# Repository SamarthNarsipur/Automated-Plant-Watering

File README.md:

Automated Plant Care v1 

yo, welcome to version 1! i built a custom arduino nano backpack shield because i wanted something sleek and tiny that won't look like a giant brick sitting next to my small plants.

what this hardware actually does

basically, i always forget to water my plants. so this board has a soil moisture sensor probe that sits in the dirt and acts like its eyes. if the dirt gets super dry, the arduino detects it and flashes a signal over to a pn2222a transistor switch. the transistor acts like an inline electronic gate keeper, allowing current to flood down into a mini 5v submersible water pump to give the plant a quick 4-second drink. then it sleeps for a minute and loops forever.
it is completely autonomous so my plants can survive my terrible memory.
i also left some digital and analog pins wide open on the nano footprint header layout. that way, if i want to upgrade it later down the line, i can easily breakout wires for an oled screen display to track live moisture metrics or plug in a second pump channel for another plant pot without rebuilding the entire power switching grid from scratch.

how to set it up

to build this thing yourself, you just need to get the custom fiberglass pcb manufactured using the production files included in this repository. once the board arrives in your mail, grab a basic soldering iron kit and solder the male pin headers for the nano, the small 1k ohm resistor, and the npn switching transistor right into their labeled places.
after the soldering is finished, just pop your arduino nano into the sockets, hook up your external 5v pump wires and moisture probe line to the terminal plugs, and use the arduino ide software on your laptop to upload the main code script down a standard usb cable.

files in this repo

• Gerbers_v2.zip - the actual production blueprints for the factory machines to print out the copper lines and fiberglass layers.
• main.ino - the tiny script that tells the microcontroller when to flip the switch.
• BOM.md - the shopping list and links for parts (plus a soldering iron kit because i dont have any solder wire at home yet lol).
built for hack club forge! 

onshape links for the case
1. https://cad.onshape.com/documents/dc3bb86a8ae5408e919ddfb3/w/a6c21399b65a292ff43e633e/e/870f76d3df2bffd9df0bdc23
2. https://cad.onshape.com/documents/dc3bb86a8ae5408e919ddfb3/w/a6c21399b65a292ff43e633e/e/acd912c24c61a0c706c50cb3
# Bill of Materials (BOM) & Budget - Automated Plant Care v1

| Designator | Component Name | Description / Package | Qty | Cost (INR) | Cost (USD Approx.) | Direct Purchase Link |
| :--- | :--- | :--- | :--- | :--- | :--- | :--- |
| **A1** | Arduino Nano R3 | ATmega328P MCU (Unsoldered headers) | 1 | ₹229.00 | $2.75 | [Robu Arduino Nano Page](https://robu.in/product/arduino-nano-board-r3-ch340-chip-with-usb-cable-solderedarduino-nano-r3-usb-cable/) |
| **Q1** | PN2222A / 2N2222 | NPN Bipolar Switching Transistor (TO-92) | 1 | ₹2.25 | $0.03 | [Robu 2N2222 Transistor Page](https://robu.in/product/2n2222a-slkorslkormicro-elec-40v-600ma-npn-to-92-bipolar-bjt-rohs/) |
| **R1** | Through-Hole Resistor | 1k Ohm Metal Film Axial Resistor (1/4W Kit) | 1 | ₹299.00 | $3.60 | [Robu Resistor Kit Page](https://robu.in/product/100pcs-1-4w-metal-film-resistors-assortment-for-diy-electronic-projects-and-experiments-2/) |
| **J3 / J4** | 2.54mm Breakaway Headers | Single Row Straight Male Pin Header Strip | 1 | ₹15.00 | $0.18 | [Robu Pin Header Page](https://robu.in/product/2-54mm-1x40-pin-male-single-row-straight-long-header-strip-pack-of-3/) |
| **External** | Soil Moisture Sensor | Soil Humidity Meter / Probe Module Kit | 1 | ₹125.00 | $1.50 | [Robu Moisture Sensor Page](https://robu.in/product/soil-moisture-module-soil-moisture-detection/) |
| **External** | Mini Water Pump | 3V-5V Micro Submersible DC Motor Water Pump | 1 | ₹145.00 | $1.75 | [Robu Mini Pump Page](https://robu.in/product/wps27-12v-dc-1l-min-mini-water-pump/) |
| **Tools** | Soldering Iron Kit | 25W Soldering Iron Combo Kit with Accessories | 1 | ₹739.00 | $8.90 | [Robu Soldering Kit Page](https://robu.in/product/soldering-iron-kit-3-in-1/) |
| **Prototyping**| Breadboard | Solderless Breadboard (830 Points / Full Size) | 1 | ₹99.00 | $1.20 | [Direct Product Link](https://robu.in/product/mb102-830-points-solderless-prototype-pcb-breadboard-high-quality/) |
| **Wires - MM**| Jumper Wires M-M | Male-to-Male DuPont Ribbon Cable (40-Pin 30cm) | 1 | ₹79.00 | $0.95 | [Direct Product Link](https://robu.in/product/male-to-male-jumper-wires-40-pin-30cm/) |
| **Wires - MF**| Jumper Wires M-F | Male-to-Female DuPont Ribbon Cable (40-Pin 20cm) | 1 | ₹49.00 | $0.60 | [Direct Product Link](https://robu.in/product/male-to-female-jumper-wires-40pcs-20cm/) |
| **Wires - FF**| Jumper Wires F-F | Female-to-Female DuPont Ribbon Cable (40-Pin 20cm)| 1 | ₹49.00 | $0.60 | [Direct Product Link](https://robu.in/product/20cm-dupont-wire-color-jumper-cable-2-54mm-1p-1p-female-female-40pcs/) |

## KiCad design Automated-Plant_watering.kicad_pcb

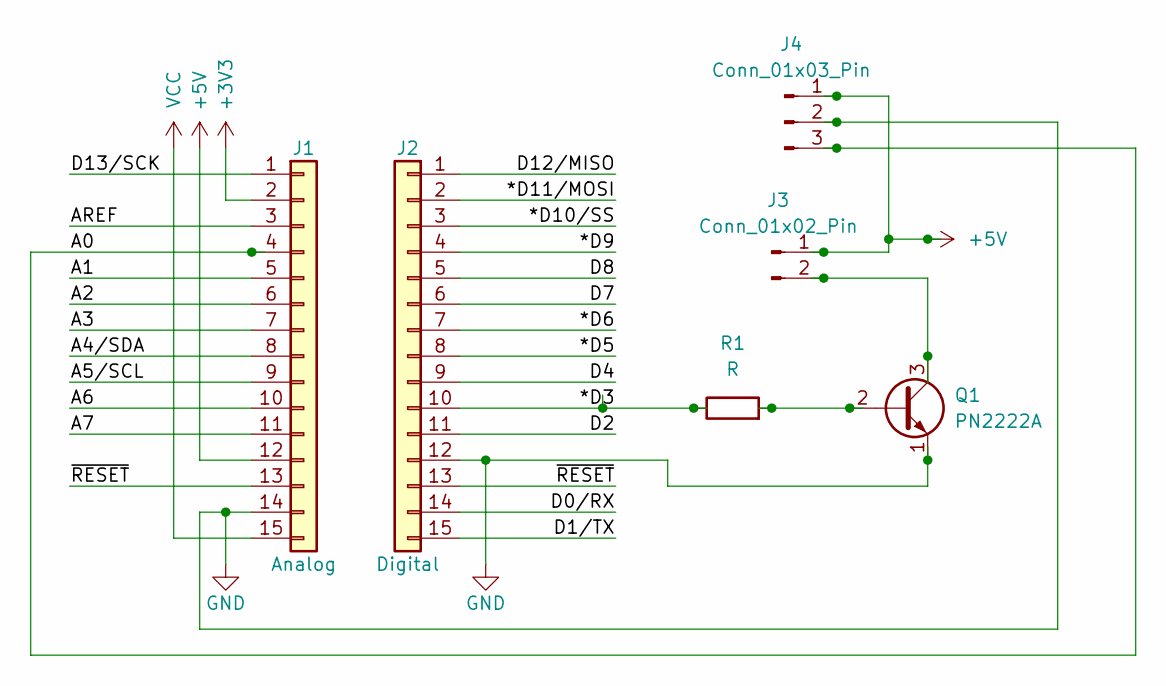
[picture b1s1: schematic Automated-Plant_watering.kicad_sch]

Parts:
J1: Analog; PinHeader_1x15_P2.54mm_Vertical
J2: Digital; PinHeader_1x15_P2.54mm_Vertical
J3: Conn_01x02_Pin; PinHeader_1x02_P2.54mm_Vertical
J4: Conn_01x03_Pin; PinHeader_1x03_P2.54mm_Vertical
Q1: PN2222A; TO-92_Inline
R1: R; R_Axial_DIN0207_L6.3mm_D2.5mm_P7.62mm_Horizontal

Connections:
+3V3: J1.2
+5V: J1.12, J3.1, J4.1
/*D3: J2.10, R1.1
/*D5: J2.8
/*D6: J2.7
/*D9: J2.4
/*D10/SS: J2.3
/*D11/MOSI: J2.2
/A0: J1.4, J4.3
/A1: J1.5
/A2: J1.6
/A3: J1.7
/A4/SDA: J1.8
/A5/SCL: J1.9
/A6: J1.10
/A7: J1.11
/AREF: J1.3
/D0/RX: J2.14
/D1/TX: J2.15
/D2: J2.11
/D4: J2.9
/D7: J2.6
/D8: J2.5
/D12/MISO: J2.1
/D13/SCK: J1.1
/~RESET: J1.13, J2.13
GND: J1.14, J2.12, J4.2, Q1.1 (E)
unnamed: J3.2, Q1.3 (C)
unnamed: Q1.2 (B), R1.2
VCC: J1.15

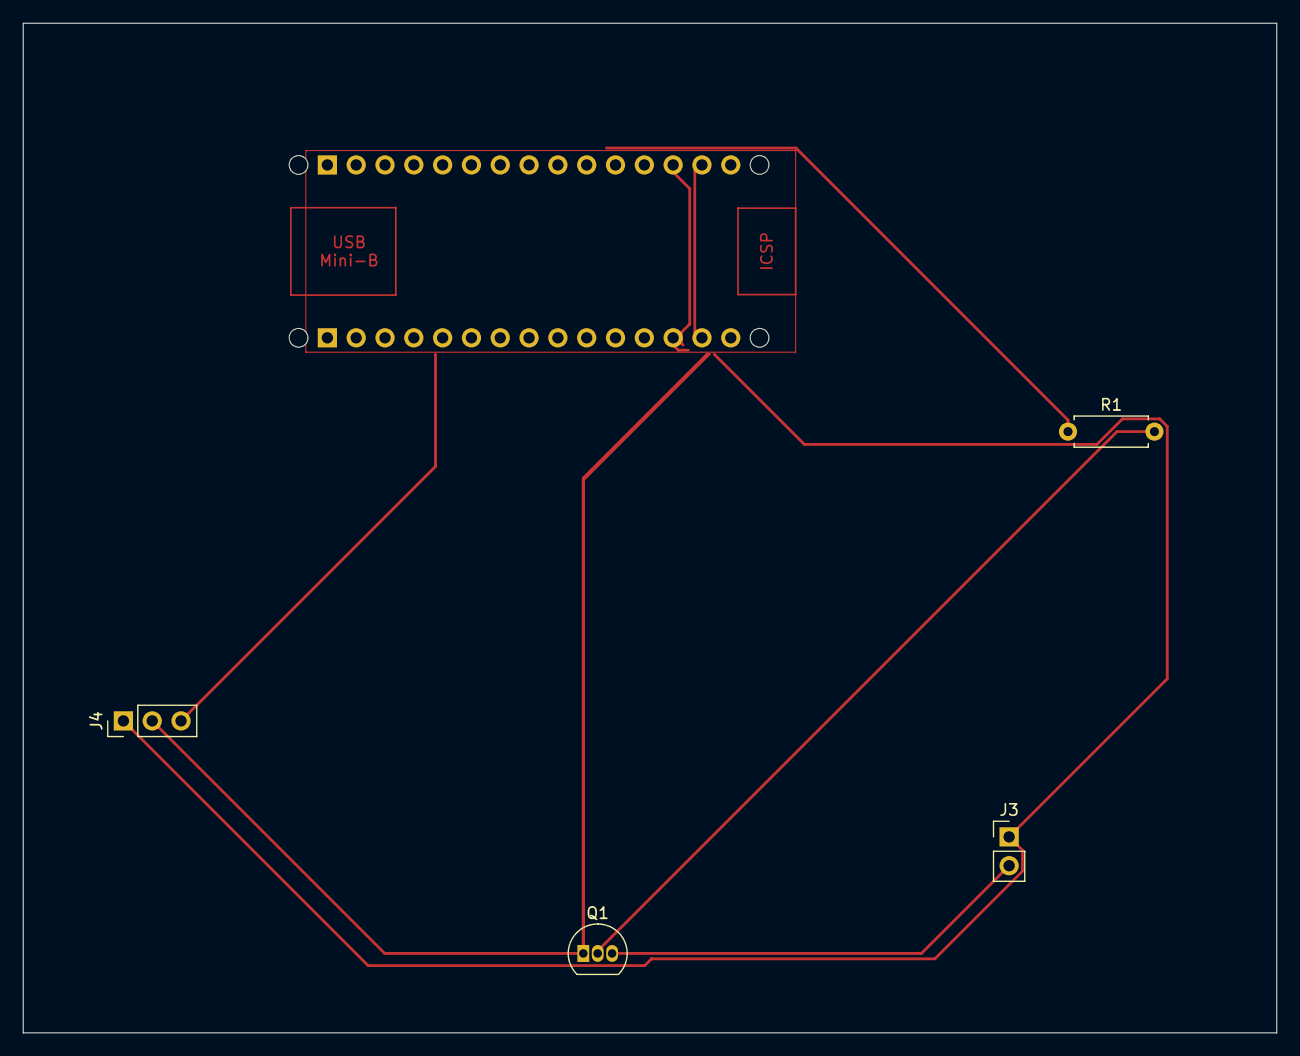
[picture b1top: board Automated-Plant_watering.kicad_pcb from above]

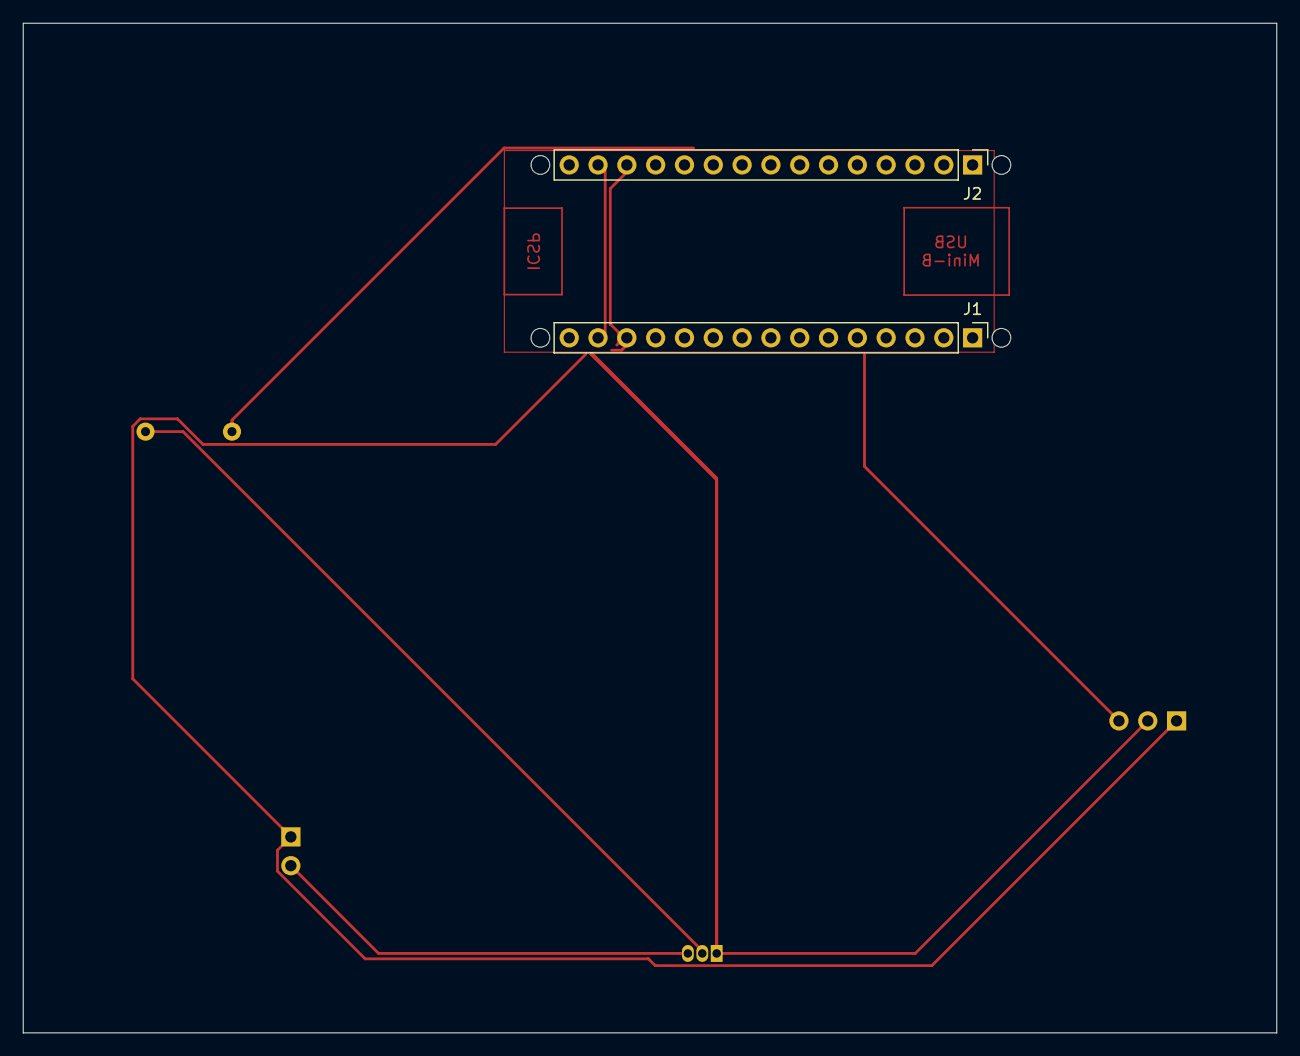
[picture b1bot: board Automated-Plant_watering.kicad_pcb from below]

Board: 2 copper layers, 110.5 x 89.0 mm, 10 parts (2 on the bottom side), 7 nets.

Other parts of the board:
MH1, MH2, MH3, MH4: MountingHole_65mil
